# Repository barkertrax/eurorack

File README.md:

# Eurorack projects

This repository contains the results of my attempts to put together a DIY modular synthesiser.

## Philosphoy

Ever the masochist, I imposed a rule on myself when I invited Eurorack modules into my life - buying finished modules ready for use from a shop is not permitted. Everything must be built. By me. Whilst self-designed circuits and PCBs are the ideal here, I decided early on I was happy to permit kits.

## Tools

These are some of the tools I've been using:

### PCB design

Update 2025: I'm now using KiCAD in preference to Eagle.

I've been using Cadsoft Eagle [http://www.cadsoftusa.com](http://www.cadsoftusa.com) to layout PCBs, mostly because it's free, and because there is a huge amount of information available online to help the novice user get to grips with the software.

For modular synth design, I found the Music Thing Modular part library incredibily useful: [http://github.com/TomWhitwell/MTM-Parts-Library](http://github.com/TomWhitwell/MTM-Parts-Library).

### PCB fabrication

Update 2025: [JLCPCB](https://jlcpcb.com) is now my PCB fabricator of choice.

After a little bit of research, I decided to try OSH Park [http://oshpark.com](http://oshpark.com) when the time came to make my first PCB. The results were very successful, so I've stuck with them since.

The downside is that you have to order at least 3 copies of each PCB, but for the sort of thing I've been making the price is still relatively low.

### Panel design

I'm using Inkscape to layout my panels: [http://inkscape.org/en/](http://inkscape.org/en/).

### Panel fabrication

Rather than going for the classic aluminium/steel panel look I decided to go with coloured acrylic panels instead. I am using Ponoko to manufacture these: [http://www.ponoko.com](http://www.ponoko.com)

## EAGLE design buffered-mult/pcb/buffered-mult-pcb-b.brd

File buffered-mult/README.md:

# Buffered Multiple

Every modular system needs a few multiples, and for my 2nd PCB design I decided to make a PCB for a circuit posted on the Muffwiggler forum.

My initial plan was to try and build something comparable to the [Intelijel Buff Mult](http://www.intellijel.com/eurorack-modules/buff-mult/), which is a 2HP-wide implementation. However, after a bit research I saw that Intelijel are using 2 stacked PCBs to manage this width. After a bit of faffing around I realised that I couldn't do something similar as the space required by the 8 jack sockets and hardware to connect the PCBs would exceed the 100mm limit imposed by the free version of Eagle. So on that basis, I am making a 3HP version using a single PCB.

## Current status

* PCB: completed and tested
* Panel: completed

## Resources

* [Buffered mults](http://www.modwiggler.com/forum/viewtopic.php?t=74951) - The circuit designed by Muffwiggler, daverj, is given on page 2 of this thread.

## Notes

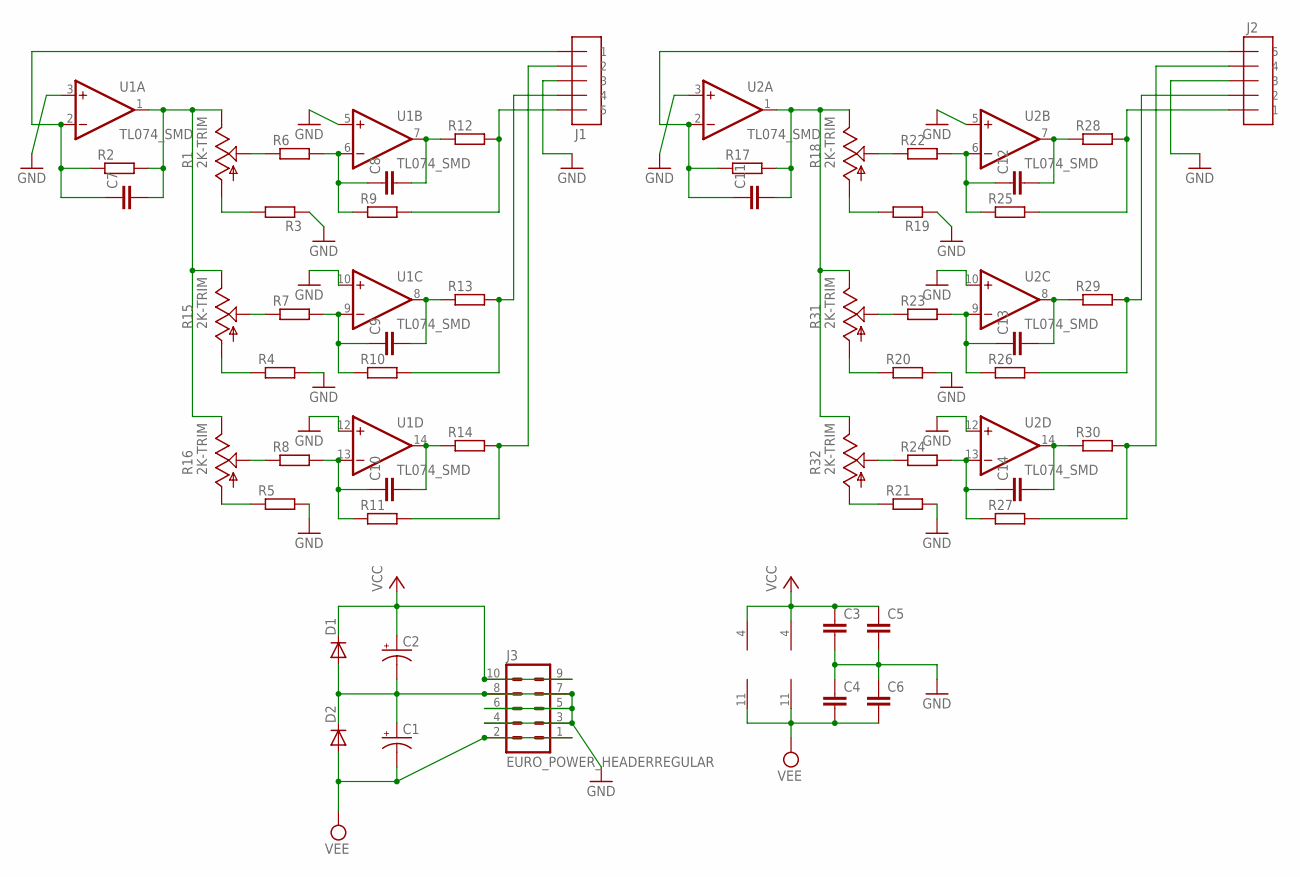
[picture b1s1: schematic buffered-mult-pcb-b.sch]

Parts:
C1, C2: CPOL-USD; PANASONIC_D
C3, C4, C5, C6, C7, C8, C9, C10, C11, C12, C13, C14: C-EUC0603; C0603
D1, D2: DIODE-SOD123; SOD123
J1, J2: 5X1_2_54_HEADER
J3: EURO_POWER_HEADERREGULAR; EURO_POWER_HEADER
R1, R15, R16, R18, R31, R32: 2K-TRIM; BOURNS_TRIM_3303X3_SMD
R2, R3, R4, R5, R6, R7, R8, R9, R10, R11, R12, R13, R14, R17, R19, R20, R21, R22, R23, R24, R25, R26, R27, R28, R29, R30: R-EU_R0603; R0603
U1, U2: TL074_SMD; SO14

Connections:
GND: C1.+, C2.-, C3.2, C4.1, C5.2, C6.1, D1.A, D2.C, J1.3, J2.3, J3.3, J3.4, J3.5, J3.6, J3.7, J3.8, R3.1, R4.2, R5.2, R19.1, R20.2, R21.2, U1.3 (+IN), U1.5 (+IN), U1.10 (+IN), U1.12 (+IN), U2.3 (+IN), U2.5 (+IN), U2.10 (+IN), U2.12 (+IN)
unnamed: C7.1, J1.1, R2.1, U1.2 (-IN)
unnamed: C7.2, R1.1 (E), R2.2, R15.1 (E), R16.1 (E), U1.1 (OUT)
unnamed: R1.2 (S), R6.1
unnamed: C8.1, R6.2, R9.1, U1.6 (-IN)
unnamed: C8.2, R12.1, U1.7 (OUT)
unnamed: J1.5, R9.2, R12.2
unnamed: R7.1, R15.2 (S)
unnamed: R1.3 (A), R3.2
unnamed: C9.1, R7.2, R10.1, U1.9 (-IN)
unnamed: C9.2, R13.1, U1.8 (OUT)
unnamed: J1.4, R10.2, R13.2
unnamed: J1.2, R11.2, R14.2
unnamed: R4.1, R15.3 (A)
unnamed: R8.1, R16.2 (S)
unnamed: C10.1, R8.2, R11.1, U1.13 (-IN)
unnamed: R5.1, R16.3 (A)
unnamed: C10.2, R14.1, U1.14 (OUT)
unnamed: C11.1, J2.5, R17.1, U2.2 (-IN)
unnamed: C11.2, R17.2, R18.1 (E), R31.1 (E), R32.1 (E), U2.1 (OUT)
unnamed: R18.2 (S), R22.1
unnamed: C12.1, R22.2, R25.1, U2.6 (-IN)
unnamed: C12.2, R28.1, U2.7 (OUT)
unnamed: J2.1, R25.2, R28.2
unnamed: R18.3 (A), R19.2
unnamed: R23.1, R31.2 (S)
unnamed: C13.1, R23.2, R26.1, U2.9 (-IN)
unnamed: C13.2, R29.1, U2.8 (OUT)
unnamed: J2.2, R26.2, R29.2
unnamed: R20.1, R31.3 (A)
unnamed: R24.1, R32.2 (S)
unnamed: C14.1, R24.2, R27.1, U2.13 (-IN)
unnamed: R21.1, R32.3 (A)
unnamed: C14.2, R30.1, U2.14 (OUT)
unnamed: J2.4, R27.2, R30.2
VCC: C2.+, C3.1, C5.1, D1.C, J3.9, J3.10, U1.4 (V+), U2.4 (V+)
VEE: C1.-, C4.2, C6.2, D2.A, J3.1, J3.2, U1.11 (V-), U2.11 (V-)

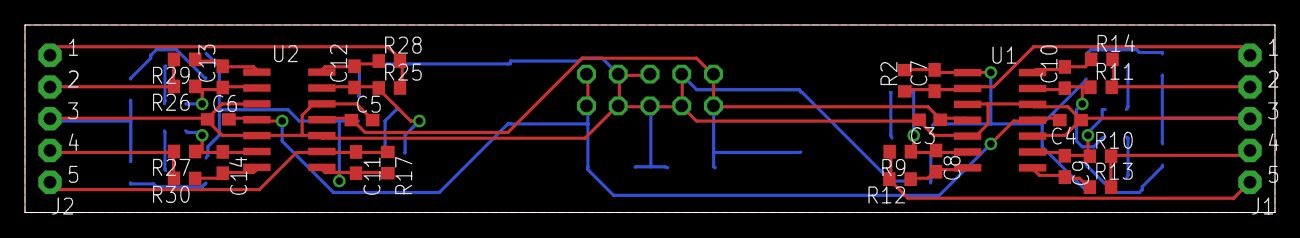
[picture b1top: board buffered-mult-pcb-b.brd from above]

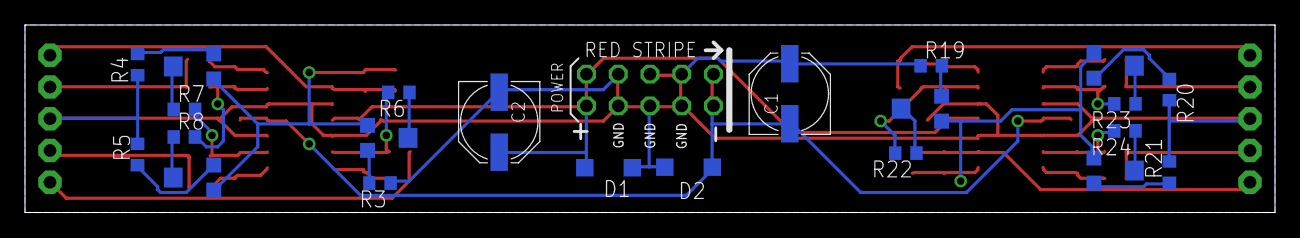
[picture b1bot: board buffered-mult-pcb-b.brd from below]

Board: 2 copper layers, 100.0 x 15.0 mm, 53 parts (23 on the bottom side), 37 nets.

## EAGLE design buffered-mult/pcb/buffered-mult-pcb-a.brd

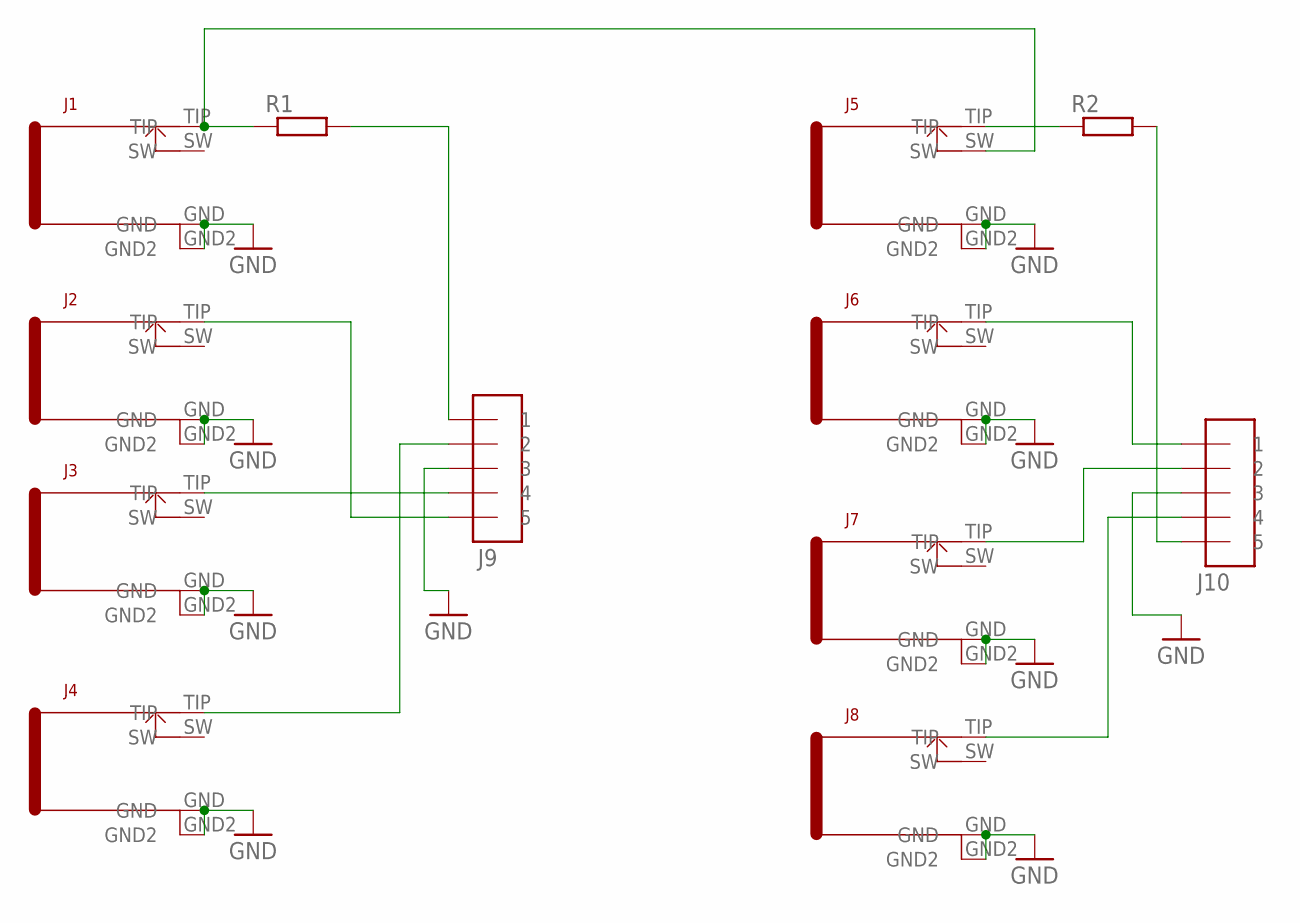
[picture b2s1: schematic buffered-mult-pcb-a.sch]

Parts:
J1, J2, J3, J4, J5, J6, J7, J8: WQP_PJ_301BM
J9, J10: 5X1_2_54_HEADER
R1, R2: R-EU_R0603; R0603

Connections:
GND: J1.GND, J1.GND2, J2.GND, J2.GND2, J3.GND, J3.GND2, J4.GND, J4.GND2, J5.GND, J5.GND2, J6.GND, J6.GND2, J7.GND, J7.GND2, J8.GND, J8.GND2, J9.3, J10.3
unnamed: J2.TIP, J9.5
unnamed: J3.TIP, J9.4
unnamed: J4.TIP, J9.2
unnamed: J10.5, R2.2
unnamed: J7.TIP, J10.2
unnamed: J8.TIP, J10.4
unnamed: J6.TIP, J10.1
unnamed: J1.TIP, J5.SW, R1.1
unnamed: J9.1, R1.2
unnamed: J5.TIP, R2.1

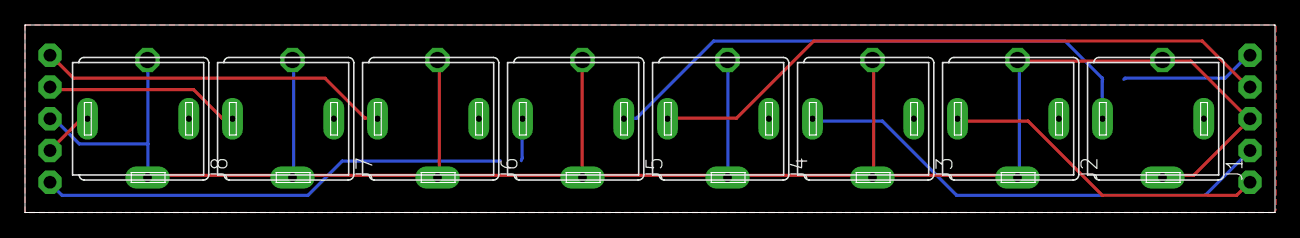
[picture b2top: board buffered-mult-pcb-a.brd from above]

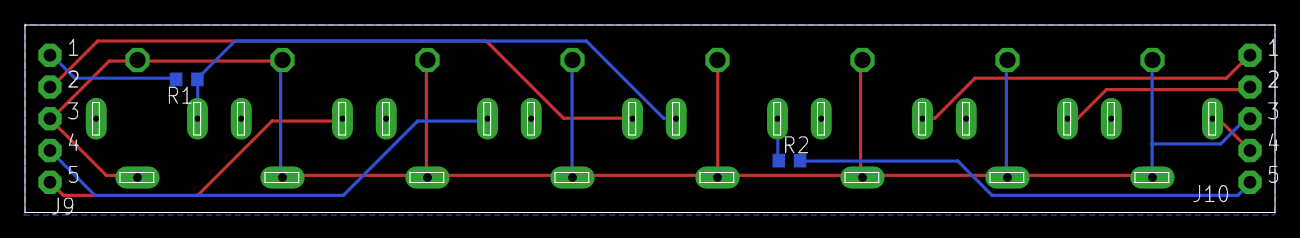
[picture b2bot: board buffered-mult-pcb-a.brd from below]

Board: 2 copper layers, 100.0 x 15.0 mm, 12 parts (4 on the bottom side), 11 nets.

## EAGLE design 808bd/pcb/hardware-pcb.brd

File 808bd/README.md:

# 808 Bass Drum

Some years ago, I bought a PCB online that implements the bass drum circuit from the classic Roland TR808. The PCB is still available to purchase: [https://www.tindie.com/products/jmej/808-kick-drum-clone-pcb/](https://www.tindie.com/products/jmej/808-kick-drum-clone-pcb/).

A thread on Muffwiggler discusses the PCB: [http://www.modwiggler.com/forum/viewtopic.php?t=54149](http://www.modwiggler.com/forum/viewtopic.php?t=54149)

As part of my modular DIY effort, I decided to finally populate the PCB and turn it into a eurorack module for use in my system. 

As a gentle introduction to PCB design, I designed a simple 'host PCB' in Eagle to house the hardware (3 x jacks; 4 x pots) and support the main PCB.

## Current status

* Main PCB: fully populated and tested - works.
* Host PCB: Built - works!
* Panel: Complete

## Possible extension

A Muffwiggler user took the same PCB and added voltage control for all the pots. His project "Thumper" is discussed here: [http://www.modwiggler.com/forum/viewtopic.php?t=107527](http://www.modwiggler.com/forum/viewtopic.php?t=107527)

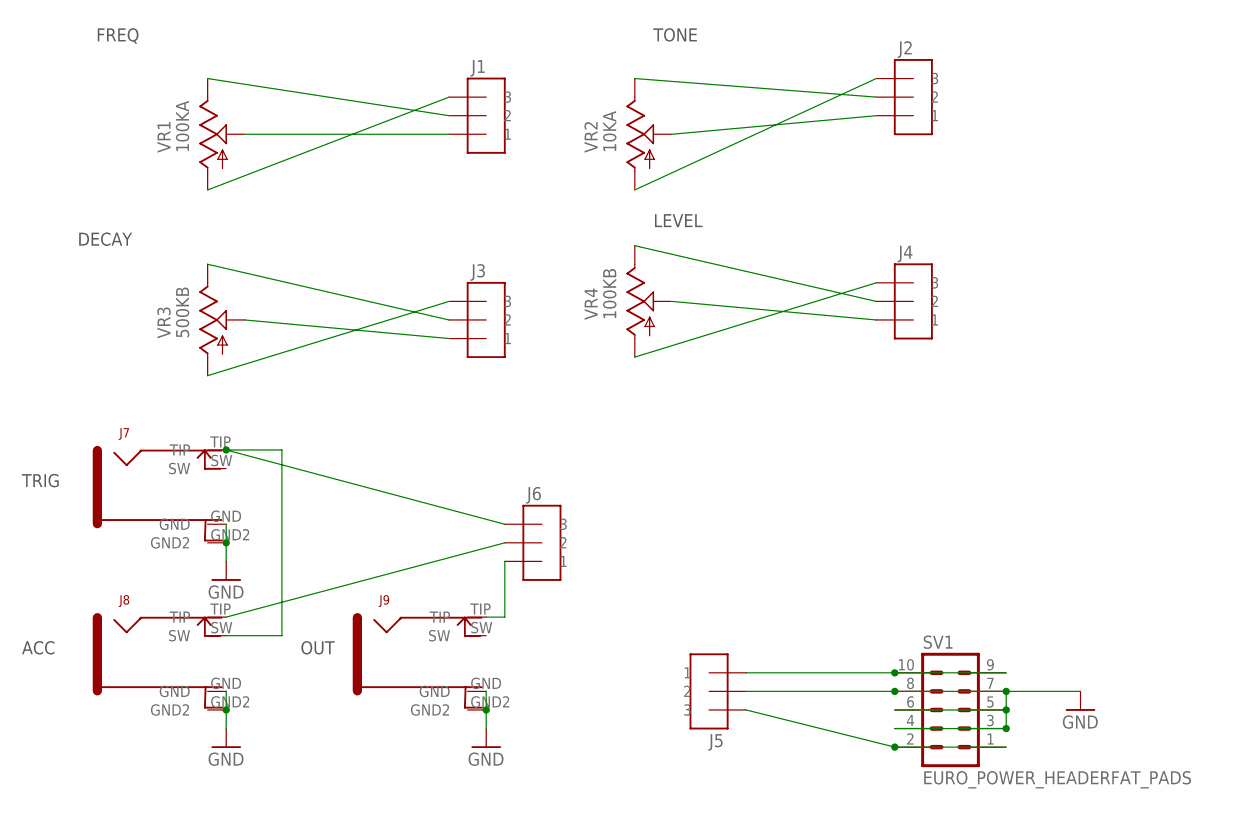
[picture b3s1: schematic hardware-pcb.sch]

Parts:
J1, J2, J3, J4, J6: 3X1_2_54_HEADER
J5: PWR; 3X1_2_54_HEADER
J7, J8, J9: WQP_PJ_301BM
SV1: EURO_POWER_HEADERFAT_PADS; EURO_PWR_HEADER_FAT
VR1: 100KA; ALPS_POT_VERTICAL_PS
VR2: 10KA; ALPS_POT_VERTICAL_PS
VR3: 500KB; ALPS_POT_VERTICAL_PS
VR4: 100KB; ALPS_POT_VERTICAL_PS

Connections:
GND: J5.2, J7.GND, J7.GND2, J8.GND, J8.GND2, J9.GND, J9.GND2, SV1.3, SV1.4, SV1.5, SV1.6, SV1.7, SV1.8
J1: J1.3, VR1.P$1 (A)
unnamed: J5.3, SV1.1, SV1.2
unnamed: J2.2, VR2.P$2 (E)
unnamed: J2.1, VR2.P$3 (S)
unnamed: J2.3, VR2.P$1 (A)
unnamed: J5.1, SV1.9, SV1.10
unnamed: J1.2, VR1.P$2 (E)
unnamed: J1.1, VR1.P$3 (S)
unnamed: J3.2, VR3.P$2 (E)
unnamed: J3.1, VR3.P$3 (S)
unnamed: J4.2, VR4.P$2 (E)
unnamed: J4.1, VR4.P$3 (S)
unnamed: J3.3, VR3.P$1 (A)
unnamed: J4.3, VR4.P$1 (A)
unnamed: J6.3, J7.TIP, J8.SW
unnamed: J6.2, J8.TIP
unnamed: J6.1, J9.TIP

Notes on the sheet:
FREQ
DECAY
TONE
LEVEL
TRIG
ACC
OUT

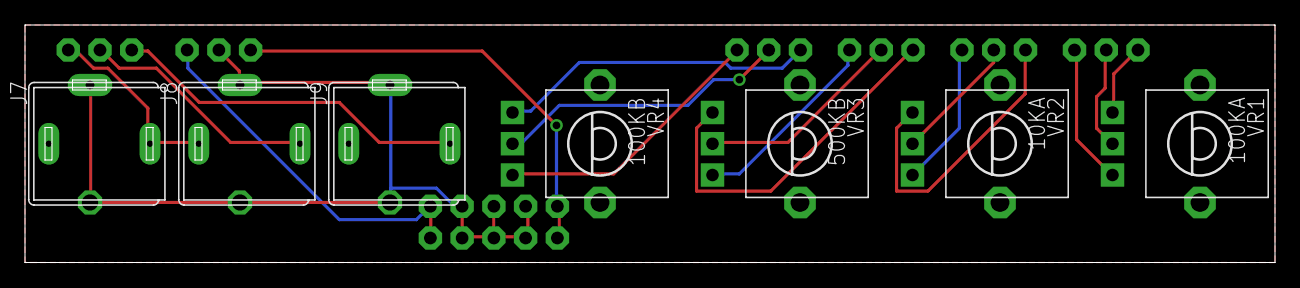
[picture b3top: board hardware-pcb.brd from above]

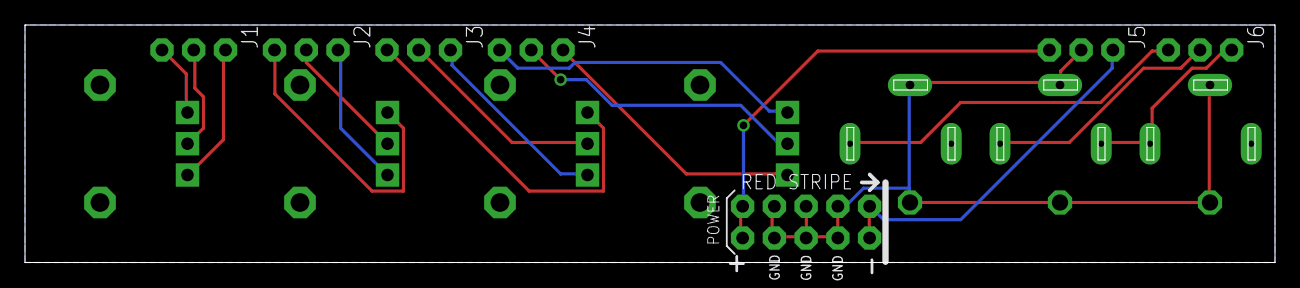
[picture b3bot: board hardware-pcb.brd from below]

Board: 2 copper layers, 100.0 x 19.0 mm, 14 parts (7 on the bottom side), 18 nets.

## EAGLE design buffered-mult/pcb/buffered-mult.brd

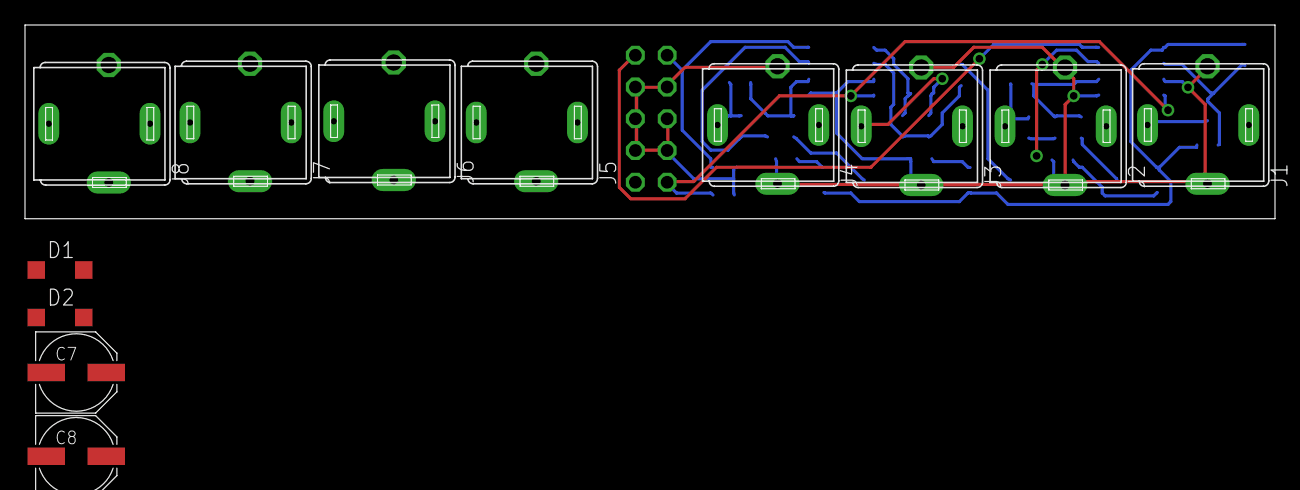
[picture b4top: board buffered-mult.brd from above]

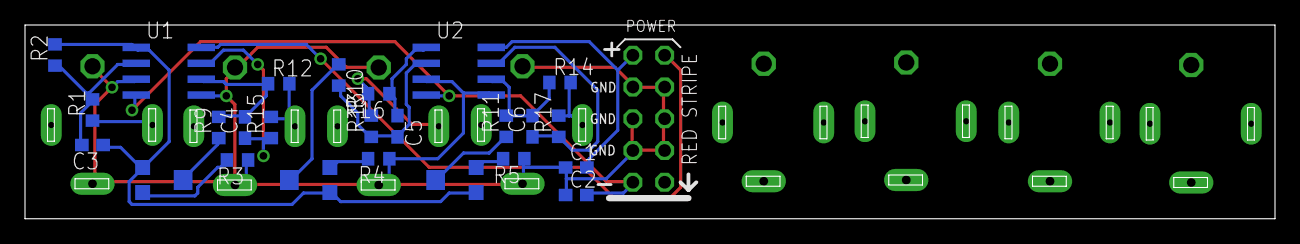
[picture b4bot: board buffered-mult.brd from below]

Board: 2 copper layers, 100.0 x 15.5 mm, 38 parts (26 on the bottom side), 23 nets.

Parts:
C1, C2, C3, C4, C5, C6: C0603
C7, C8: PANASONIC_D
D1, D2: SOD123
J1, J2, J3, J4, J5, J6, J7, J8: WQP_PJ_301BM
R1, R2, R3, R4, R5, R9, R10, R11, R12, R13, R14, R15, R16, R17: R0603
R6, R7, R8: 2K-TRIM; BOURNS_TRIM_3303X3_SMD
SV1: EURO_POWER_HEADERREGULAR; EURO_POWER_HEADER
U1, U2: TL072_SMD; SO08

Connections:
GND: C1.1, C2.1, C7.-, C8.+, D1.A, D2.C, J1.GND, J1.GND2, J2.GND, J2.GND2, J3.GND, J3.GND2, J4.GND, J4.GND2, R3.1, R4.1, R5.1, SV1.3, SV1.4, SV1.5, SV1.6, SV1.7, SV1.8, U1.3, U1.5, U2.3, U2.5
unnamed: J1.TIP, R1.1
unnamed: C3.2, R1.2, R2.1, U1.2
unnamed: C4.1, R15.1, U1.7
unnamed: R3.2, R6.3
unnamed: R4.2, R7.3
unnamed: R5.2, R8.3
unnamed: C4.2, R9.2, R12.1, U1.6
unnamed: R6.2, R9.1
unnamed: C5.2, R10.2, R13.1, U2.2
unnamed: SV1.9, SV1.10
unnamed: SV1.1, SV1.2
unnamed: C6.2, R11.2, R14.1, U2.6
unnamed: R7.2, R10.1
unnamed: R8.2, R11.1
unnamed: C3.1, R2.2, R6.1, R7.1, R8.1, U1.1
unnamed: J2.TIP, R12.2, R15.2
unnamed: C5.1, R16.1, U2.1
unnamed: J3.TIP, R13.2, R16.2
unnamed: C6.1, R17.1, U2.7
unnamed: J4.TIP, R14.2, R17.2
VCC: C1.2, C7.+, D1.C, U1.8, U2.8
VEE: C2.2, C8.-, D2.A, U1.4, U2.4

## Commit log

2015-05-04 Added 808 bass drum info
2015-05-04 Fixed 808bd markdown
2015-05-04 - Added braids-diy info
2015-05-04 Added buffered mult info
2015-05-04 Added ripples-diy info
2015-05-05 Made a second attempt at the pcb
2015-05-05 previous attempt - won't work
2015-05-13 - Updated 808BD Host BOM - v1.0 PCB sent to OSHPark
2015-05-13 - Added BOM for buffered must - Moved previous PCB attempt
2015-05-13 - Added BOM for ripples-diy
2015-05-13 - Added new module - simple-mixer
2015-05-13 - v1.0 buffered-mult PCBs uploaded to OSHPark
2015-05-13 - Ignore temp files generated by eagle
2015-05-13 - Updated readme files
2015-05-17 - Panel designs sent to Ponoko
2015-05-17 Corrected Ripples BOM - LM4040 part was incorrect (2.5V instead of 5.0V)
2015-06-05 Update to 808BD status
2026-05-31 Modernisation
2026-05-31 Improve text
2026-05-31 Text corrections
